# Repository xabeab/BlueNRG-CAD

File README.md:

BlueNRG-CAD
======
CAD files to produce the mechanical enclosure and circuits for a BLE device monitoring movement.

The mechanical parts were designed using CATIA. A student license is necessary to open the files. The STL files are available for 3D printing using PLA. 
The ACM_base_1 part is compatible with AppleWatch bands serie 4. It should be used for ankles and wrists.
The ACM_base_2 can be attached to a belt or any piece of thick clothing.

The circuit was designed using KiCad. All GERBER files are available for immediate production. A battery of around 160 mAh should be connected using a JST connector. 

This repository is part of the Activity Recognition based on Movement project, which is a complete open-source hardware and software solution of wearable BLE accelerometers + gyroscopes allowing activity recognition.

License
-------
This files are released into the public domain by its author, Xavier Beaulé.

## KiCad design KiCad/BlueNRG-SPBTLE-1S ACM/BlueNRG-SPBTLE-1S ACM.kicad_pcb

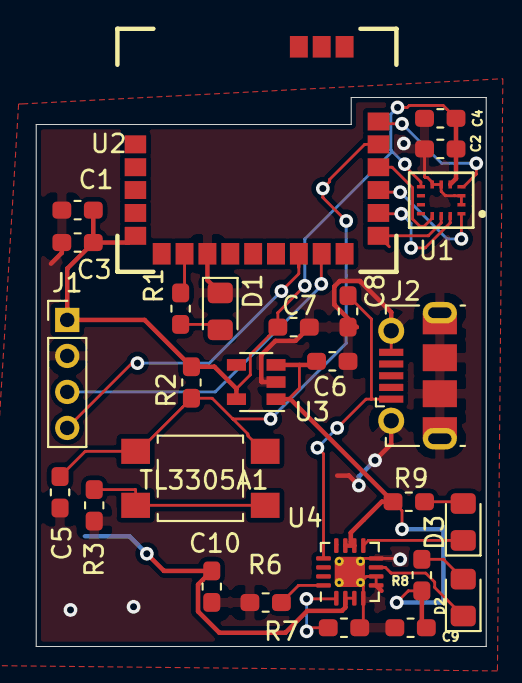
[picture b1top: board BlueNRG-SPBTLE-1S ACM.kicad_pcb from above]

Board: 2 copper layers, 25.0 x 30.5 mm, 28 parts (1 on the bottom side), 22 nets.

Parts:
C1: 2.2u; C_0603_1608Metric_Pad1.05x0.95mm_HandSolder
C2, C3, C4: 100n; C_0603_1608Metric_Pad1.05x0.95mm_HandSolder
C5: 10n; C_0603_1608Metric_Pad1.05x0.95mm_HandSolder
C6, C7, C8: 1u; C_0603_1608Metric_Pad1.05x0.95mm_HandSolder
C9, C10: 4.7u; C_0603_1608Metric_Pad1.05x0.95mm_HandSolder
D1, D2, D3: LED; LED_0805_2012Metric_Pad1.15x1.40mm_HandSolder
J1: Conn_01x04_Female; Socket_Strip_Straight_1x04_Pitch2.00mm
J2: USB_B_Micro; USB_Micro-B_Molex-105017-0001
J3: Conn_01x02_Female; JST_PH_S2B-PH-SM4-TB_1x02-1MP_P2.00mm_Horizontal
R1: 680; R_0603_1608Metric_Pad1.05x0.95mm_HandSolder
R2, R3: 100k; R_0603_1608Metric_Pad1.05x0.95mm_HandSolder
R6: 11.5k; R_0603_1608Metric_Pad1.05x0.95mm_HandSolder
R7: 10k; R_0603_1608Metric_Pad1.05x0.95mm_HandSolder
R8, R9: 2k; R_0603_1608Metric_Pad1.05x0.95mm_HandSolder
TL3305A1: SW_Push_Dual; SW_SPST_TL3305A
U1: LSM6DS3
U2: SPBTLE-1S-Custom_Library; SPBTLE-1S
U3: TLV70033_SOT23-5; SOT-23-5
U4: BQ24232; VQFN-16-1EP_3x3mm_P0.5mm_EP1.68x1.68mm_ThermalVias

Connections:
DIO12-INT: U1.4, U2.20
GND: C1.2, C2.1, C3.2, C4.2, C5.2, C6.1, C7.2, C8.2, C9.1, C10.1, D1.1, J1.2, J2.5, J2.6, J3.2, R3.2, R6.1, R7.2, U1.2, U1.3, U1.6, U1.7, U2.8, U3.2, U4.4, U4.5, U4.6, U4.8, U4.17
JTCK-SWCTK: J1.4, U2.12
JTMS-SWTDIO: J1.3, U2.13
unnamed: C5.1, R2.2, TL3305A1.2, U2.19
unnamed: C8.1, J2.1, U4.13
unnamed: C10.2, J3.1, U4.2, U4.3
unnamed: D1.2, R1.2
unnamed: D2.1, U4.7
unnamed: D2.2, R8.1
unnamed: D3.1, U4.9
unnamed: D3.2, R9.1
unnamed: R1.1, U2.7
unnamed: R3.1, TL3305A1.1
unnamed: R6.2, U4.16
unnamed: R7.1, U4.1
SPI_CLK: U1.13, U2.15
SPI_CS: U1.12, U2.18
SPI_IN: U1.1, U2.17
SPI_OUT: U1.14, U2.16
VOUT_BQ: C6.2, C9.2, R8.2, R9.2, U3.1, U3.3, U4.10, U4.11
Vdd: C1.1, C2.2, C3.1, C4.1, C7.1, J1.1, R2.1, U1.5, U1.8, U2.5, U3.5

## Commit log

2019-02-18 Initial relase. Working on the PCB for the BlueNRG-2
2019-03-03 Initial push for the SPBTLE-1S
2019-03-04 Initial PCB design done
2019-03-05 Added a push button for the RST pin and an IC for the power management
2019-03-05 Generated the gbr files for the 1st print
2019-03-18 Enclosure design using Catia
2019-03-19 Part 3 and 4 based on the Apple Watch
2019-03-26 Improved the tolerances for the white PLA
2019-04-02 The cover now is even with the rest of the enclosure
2019-04-11 Changed the band profile to the official one from Apple
2019-05-06 Made the necessary modifications for ACM v2 (circuit logic to Vbat, Vdd to SPTBLE)
2020-09-30 The first version is completed
2020-09-30 Smaller pcb. Also added charging feature
2020-09-30 Modified the charging feature
2020-09-30 Added charging capabilities to ACM PCB and removed the screws. Removed the screws from the cover
2020-09-30 Fixed the PCB layout and schematic for the charger U
2020-09-30 Changed the female connector for the battery. Changed the BQ circuitry
2020-09-30 Few changes before order
2020-09-30 Added BOM
2020-09-30 Made changes to fit the new battery
2020-09-30 Added holes to displays charging statue. Improved the fiting of the top part of the pieces
2020-09-30 Removed junk files. Added stl.
2020-09-30 Moved files up one folder
2020-09-30 Added a part for wearability on the belt
2020-09-30 Moved the librairies folder into the kicad folder
